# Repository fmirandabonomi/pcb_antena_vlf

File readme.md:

<!-- markdownlint-disable-file MD013 -->
# Antena VLF, Laboratorio de Telecomunicaciones FACET UNT

En este repositorio se encuentran los diseños de los acondicionadores de señales y módulo de adquisición de la antena de VLF desarrollada en el Laboratorio de Telecomunicaciones, FACET UNT en el periodo 2024-2025

La antena de VLF consiste en un par de antenas de lazo dispuestas en cuadratura. Cada antena de lazo es conectada a un acondicionador de señal que cumple las funciones de convertidor corriente/tensión y filtro. La salida de los acondicionadores es adquirida por un módulo de adquisición y transmitida via Ethernet hasta una computadora para su proceso y almacenamiento.

## Contenido

- **/adquisicion** : Directorio conteniendo el proyecto de KiCad del módulo de adquisición.
- **/acondicionador** : Directorio conteniendo el proyecto de KiCad del módulo acondicionador de señal.

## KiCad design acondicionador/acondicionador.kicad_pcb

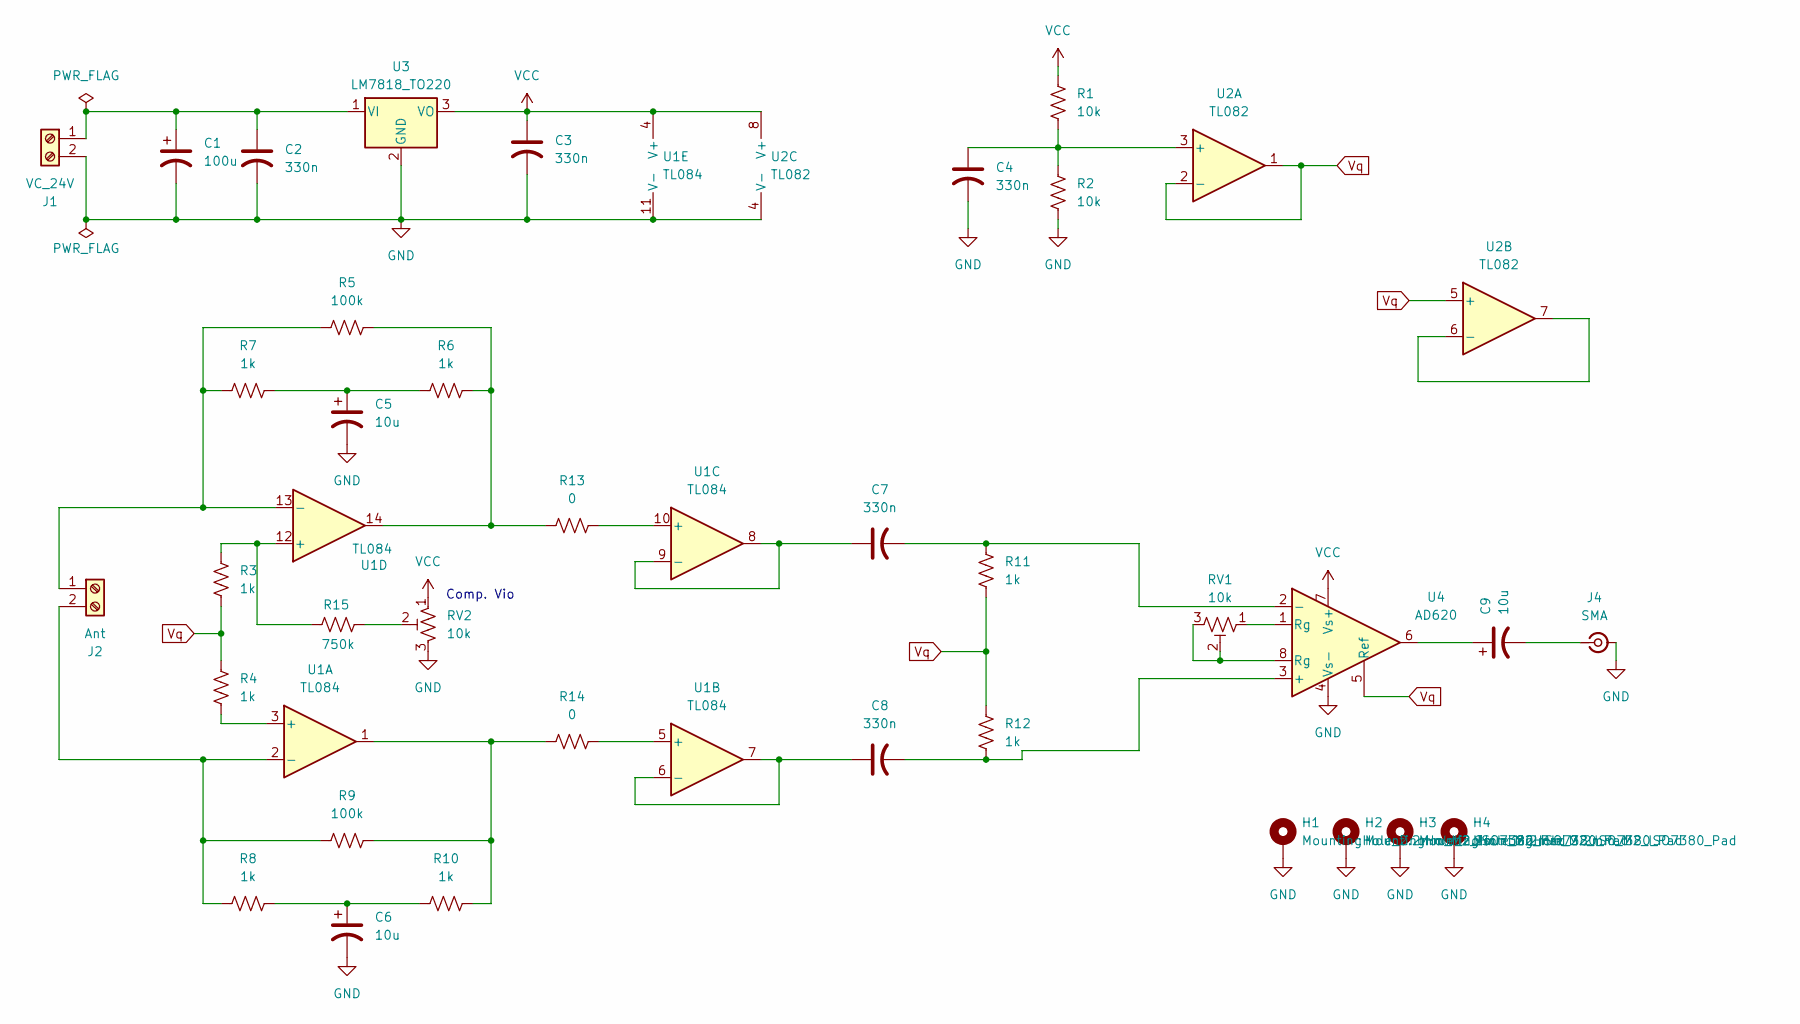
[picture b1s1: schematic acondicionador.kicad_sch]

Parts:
C1: 100u; CP_Radial_D10.0mm_P5.00mm-pad2mm2
C2, C3, C4, C7, C8: 330n; C_Disc_D5.1mm_W3.2mm_P5.00mm-pad2mm
C5, C6, C9: 10u; CP_Radial_D10.0mm_P5.00mm-pad2mm2
H1, H2, H3, H4: MountingHole_2.2mm_M2_ISO7380_Pad
J1: VC_24V; TerminalBlock_MetzConnect_Type011_RT05502HBLC_1x02_P5.00mm_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
J2: Ant; TerminalBlock_MetzConnect_Type011_RT05502HBLC_1x02_P5.00mm_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
J4: SMA; SMA_Samtec_SMA-J-P-H-ST-EM1_EdgeMount
R1, R2: 10k; R_Axial_DIN0207_L6.3mm_D2.5mm_P10.16mm_Horizontal-pad2mm
R3, R4: 1k; R_Axial_DIN0207_L6.3mm_D2.5mm_P15.24mm_Horizontal-pad2mm
R5, R9: 100k; R_Axial_DIN0207_L6.3mm_D2.5mm_P10.16mm_Horizontal-pad2mm
R6, R7, R8, R10, R11, R12: 1k; R_Axial_DIN0207_L6.3mm_D2.5mm_P10.16mm_Horizontal-pad2mm
R13, R14: 0; R_Axial_DIN0207_L6.3mm_D2.5mm_P10.16mm_Horizontal-pad2mm
R15: 750k; R_Axial_DIN0207_L6.3mm_D2.5mm_P10.16mm_Horizontal-pad2mm
RV1, RV2: 10k; Potentiometer_Bourns_3296W_Vertical-pad2mm
U1: TL084; DIP-14_W7.62mm_LongPads-2mm
U2: TL082; DIP-8_W7.62mm_LongPads-pad2mm
U3: LM7818_TO220; TO-220-3_Vertical-pad2mm
U4: AD620; DIP-8_W7.62mm_LongPads-pad2mm

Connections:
GND: C1.2, C2.2, C3.2, C4.2, C5.2, C6.2, H1.1, H2.1, H3.1, H4.1, J1.2, J4.2 (Ext), R2.2, RV2.3, U1.11 (V-), U2.4 (V-), U3.2 (GND), U4.4 (Vs-)
unnamed: C5.1, R6.1, R7.2
unnamed: C6.1, R8.2, R10.1
unnamed: C9.1, U4.6
unnamed: C1.1, C2.1, J1.1, U3.1 (VI)
unnamed: J2.1, R5.1, R7.1, U1.13 (-)
unnamed: J2.2, R8.1, R9.1, U1.2 (-)
unnamed: C9.2, J4.1 (In)
unnamed: R9.2, R10.2, R14.1, U1.1
unnamed: R5.2, R6.2, R13.1, U1.14
unnamed: R15.2, RV2.2
unnamed: RV1.1, U4.1 (Rg)
unnamed: RV1.2, RV1.3, U4.8 (Rg)
unnamed: R4.2, U1.3 (+)
unnamed: R14.2, U1.5 (+)
unnamed: C8.1, U1.6 (-), U1.7
unnamed: R13.2, U1.10 (+)
unnamed: C7.1, U1.8, U1.9 (-)
unnamed: R3.1, R15.1, U1.12 (+)
unnamed: C4.1, R1.2, R2.1, U2.3 (+)
unnamed: U2.6 (-), U2.7
unnamed: C8.2, R12.2, U4.3 (+)
unnamed: C7.2, R11.1, U4.2 (-)
VCC: C3.1, R1.1, RV2.1, U1.4 (V+), U2.8 (V+), U3.3 (VO), U4.7 (Vs+)
Vq: R3.2, R4.1, R11.2, R12.1, U2.1, U2.2 (-), U2.5 (+), U4.5 (Ref)

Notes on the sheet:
Comp. Vio

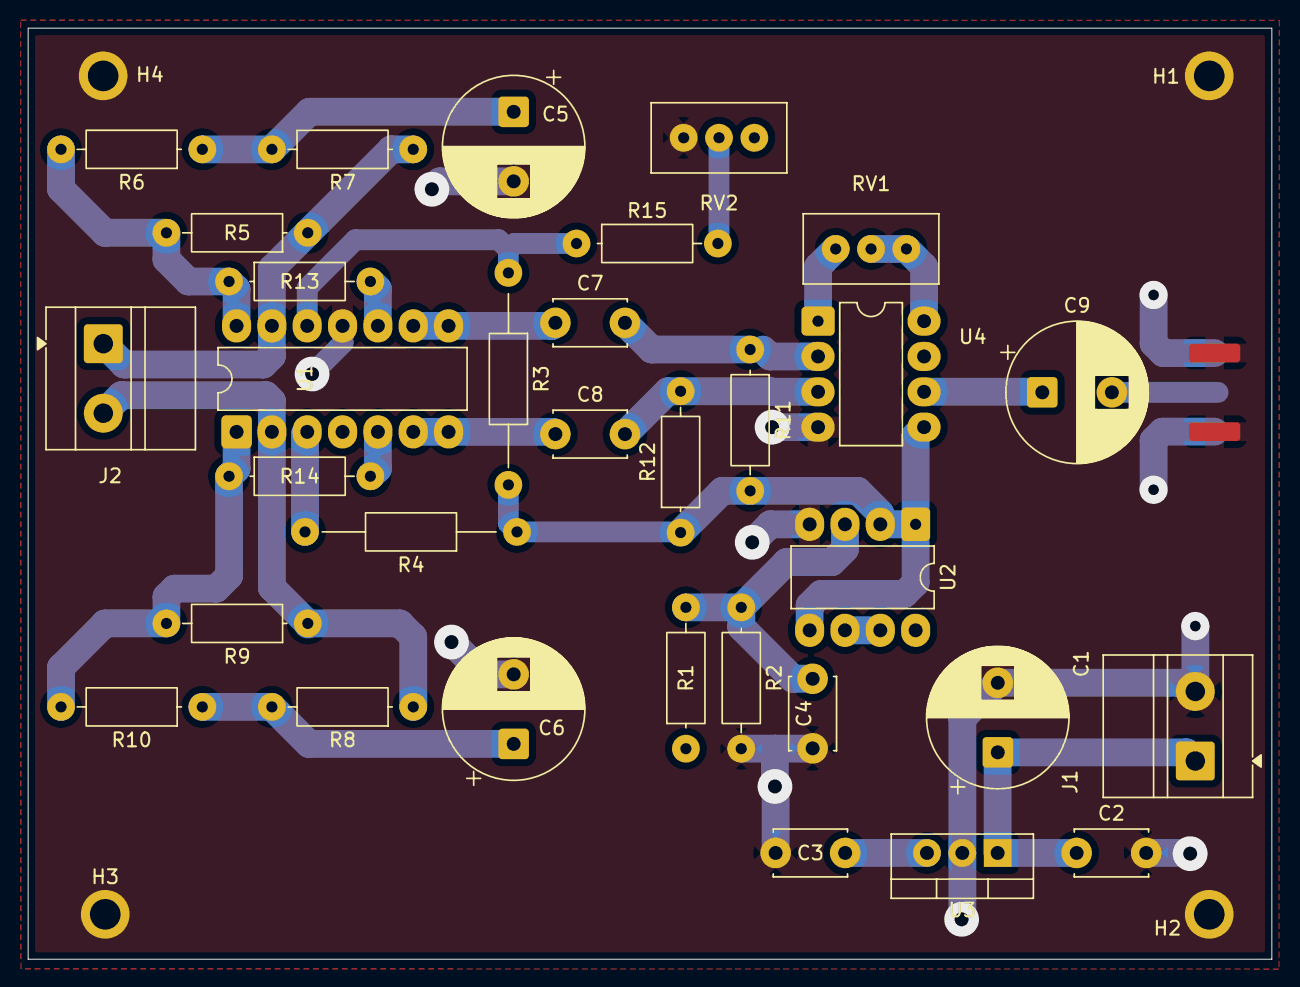
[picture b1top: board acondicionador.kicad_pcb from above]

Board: 2 copper layers, 89.4 x 66.9 mm, 37 parts (1 on the bottom side), 25 nets.

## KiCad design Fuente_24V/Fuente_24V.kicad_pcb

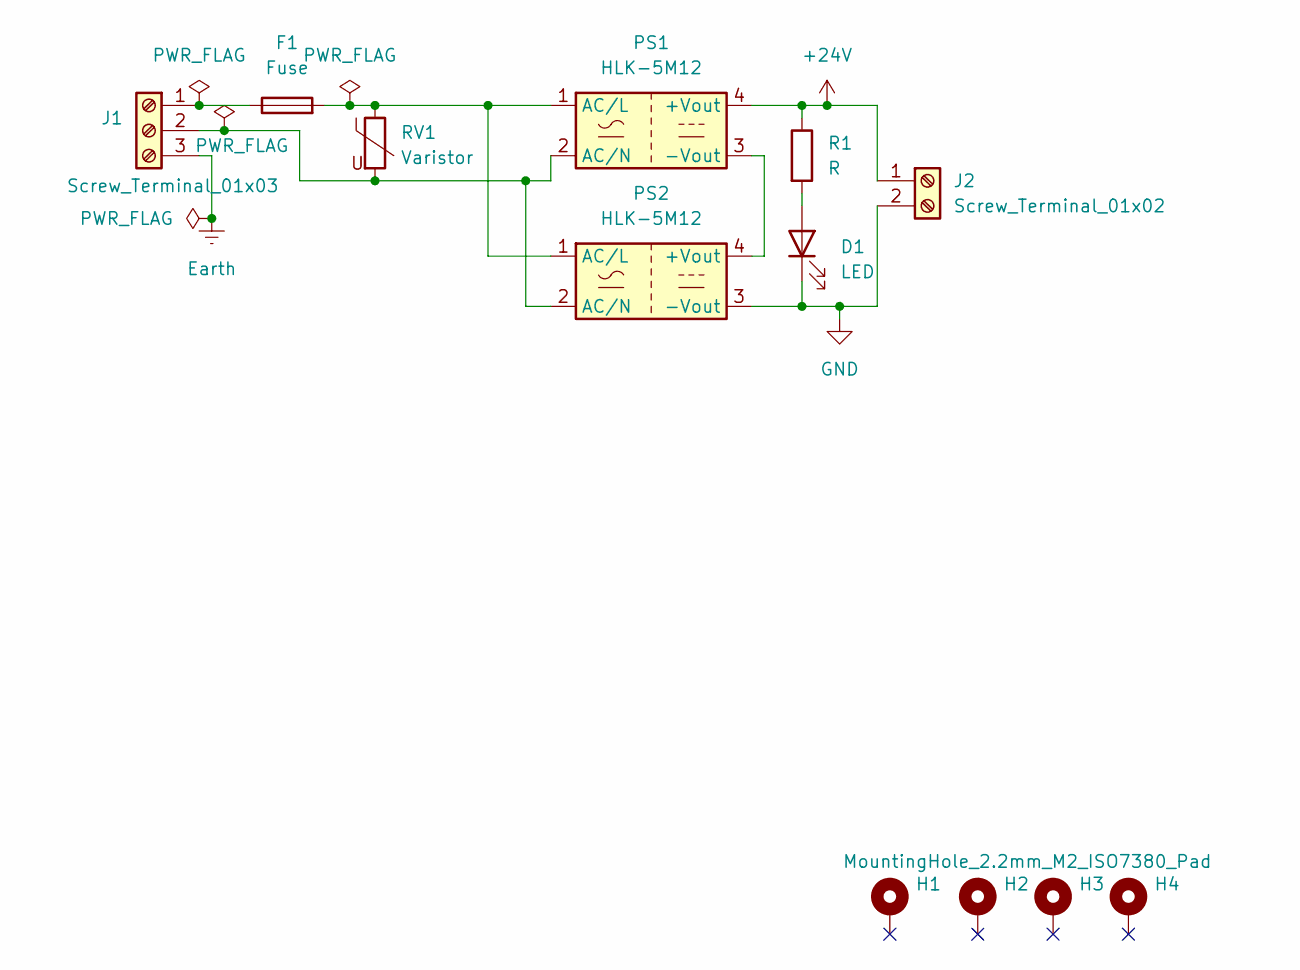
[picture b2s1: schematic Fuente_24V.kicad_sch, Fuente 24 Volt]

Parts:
D1: LED; LED_D3.0mm
F1: Fuse; Fuseholder_Cylinder-5x20mm_Schurter_0031_8201_Horizontal_Op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
H1, H2, H3, H4: MountingHole_2.2mm_M2_ISO7380_Pad
J1: Screw_Terminal_01x03; TerminalBlock_MaiXu_MX126-5.0-03P_1x03_P5.00mm
J2: Screw_Terminal_01x02; TerminalBlock_MaiXu_MX126-5.0-02P_1x02_P5.00mm
PS1, PS2: HLK-5M12; Converter_ACDC_Hi-Link_HLK-5Mxx
R1: R; R_Axial_DIN0207_L6.3mm_D2.5mm_P10.16mm_Horizontal
RV1: Varistor; RV_Disc_D12mm_W4mm_P7.5mm

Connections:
+24V: J2.1, PS1.4 (+Vout), R1.1
Earth: J1.3
GND: D1.1 (K), J2.2, PS2.3 (-Vout)
unnamed: D1.2 (A), R1.2
unnamed: F1.1, J1.1
unnamed: J1.2, PS1.2 (AC/N), PS2.2 (AC/N), RV1.2
unnamed: PS1.3 (-Vout), PS2.4 (+Vout)
unnamed: F1.2, PS1.1 (AC/L), PS2.1 (AC/L), RV1.1

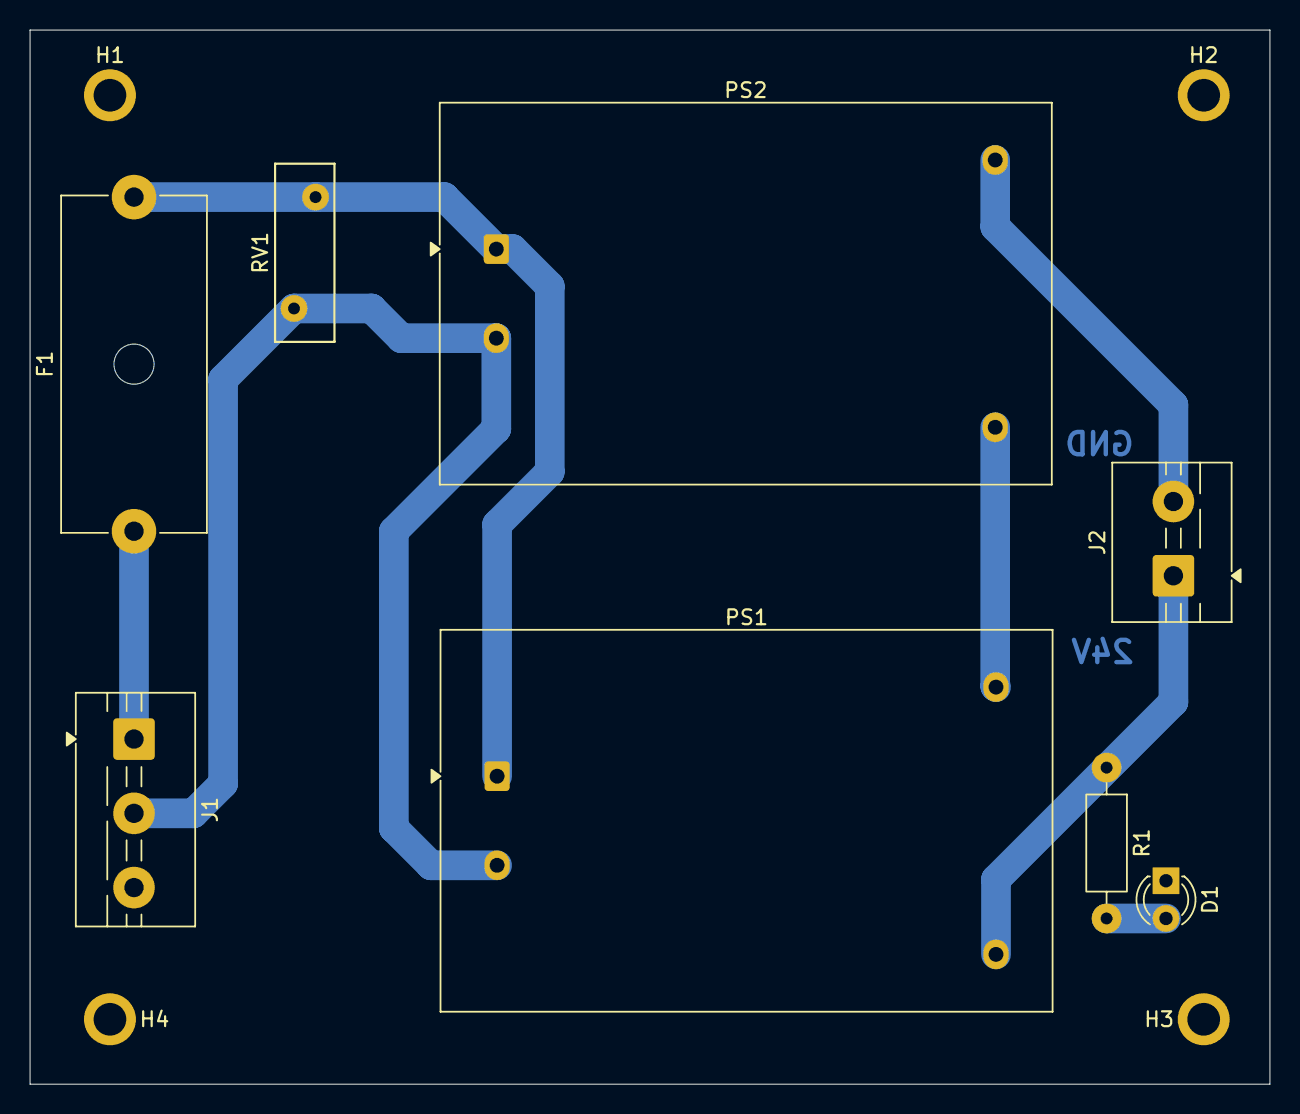
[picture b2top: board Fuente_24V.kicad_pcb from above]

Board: 2 copper layers, 83.5 x 71.0 mm, 12 parts (0 on the bottom side), 7 nets.

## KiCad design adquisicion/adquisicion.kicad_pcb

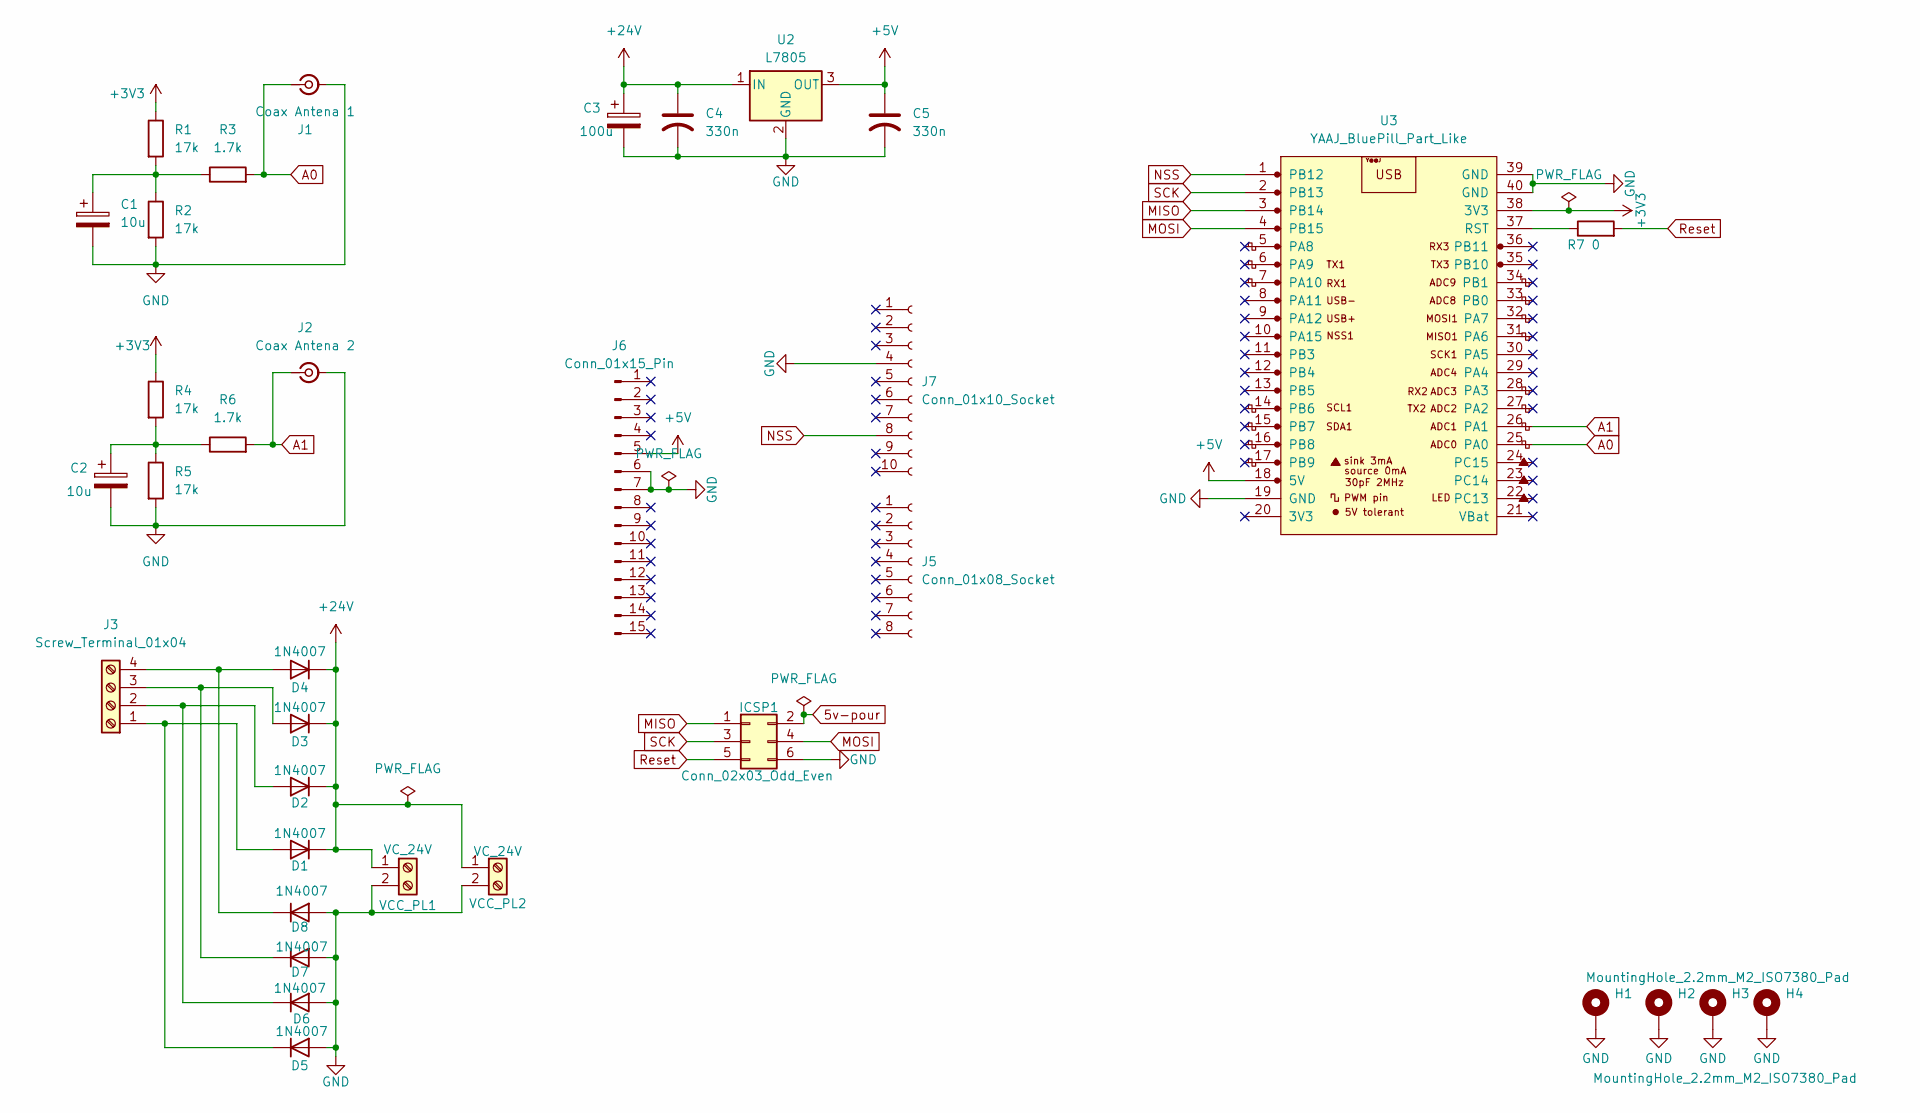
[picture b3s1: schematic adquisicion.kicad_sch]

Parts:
C1, C2: 10u; CP_Radial_D10.0mm_P5.00mm
C3: 100u; CP_Radial_D10.0mm_P5.00mm
C4, C5: 330n; C_Disc_D5.1mm_W3.2mm_P5.00mm-pad2mm
D1, D2, D3, D4, D5, D6, D7, D8: 1N4007; D_DO-41_SOD81_P10.16mm_Horizontal
H1, H2, H3, H4: MountingHole_2.2mm_M2_ISO7380_Pad
ICSP1: Conn_02x03_Odd_Even; PinHeader_2x03_P2.54mm_Vertical
J1: Coax Antena 1; SMA_Samtec_SMA-J-P-H-ST-EM1_EdgeMount
J2: Coax Antena 2; SMA_Samtec_SMA-J-P-H-ST-EM1_EdgeMount
J3: Screw_Terminal_01x04; TerminalBlock_MetzConnect_Type011_RT05504HBLC_1x04_P5.00mm_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
J5: Conn_01x08_Socket; PinHeader_1x08_P2.54mm_Vertical
J6: Conn_01x15_Pin; PinHeader_1x15_P2.54mm_Vertical
J7: Conn_01x10_Socket; PinHeader_1x10_P2.54mm_Vertical
R1, R2, R4, R5: 17k; R_Axial_DIN0207_L6.3mm_D2.5mm_P10.16mm_Horizontal-pad2mm
R3, R6: 1.7k; R_Axial_DIN0207_L6.3mm_D2.5mm_P10.16mm_Horizontal-pad2mm
R7: 0; R_Axial_DIN0207_L6.3mm_D2.5mm_P15.24mm_Horizontal-pad2mm
U2: L7805; TO-220-3_Vertical
U3: YAAJ_BluePill_Part_Like; YAAJ_BluePill_2
VCC_PL1, VCC_PL2: VC_24V; TerminalBlock_MetzConnect_Type011_RT05502HBLC_1x02_P5.00mm_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

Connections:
5v-pour: ICSP1.2
+3V3: R1.1, R4.1, U3.38 (3V3)
+5V: C5.1, J6.5, U2.3 (OUT), U3.18 (5V)
+24V: C3.1, C4.1, D1.1 (K), D2.1 (K), D3.1 (K), D4.1 (K), U2.1 (IN), VCC_PL1.1, VCC_PL2.1
A0: J1.1 (In), R3.2, U3.25 (PA0)
A1: J2.1 (In), R6.2, U3.26 (PA1)
GND: C1.2, C2.2, C3.2, C4.2, C5.2, D5.2 (A), D6.2 (A), D7.2 (A), D8.2 (A), H1.1, H2.1, H3.1, H4.1, ICSP1.6, J1.2 (Ext), J2.2 (Ext), J6.6, J6.7, J7.4, R2.2, R5.2, U2.2 (GND), U3.19 (GND), U3.39 (GND), U3.40 (GND), VCC_PL1.2, VCC_PL2.2
MISO: ICSP1.1, U3.3 (PB14)
MOSI: ICSP1.4, U3.4 (PB15)
NSS: J7.8, U3.1 (PB12)
unnamed: C1.1, R1.2, R2.1, R3.1
unnamed: C2.1, R4.2, R5.1, R6.1
unnamed: D1.2 (A), D5.1 (K), J3.1
unnamed: D2.2 (A), D6.1 (K), J3.2
unnamed: D3.2 (A), D7.1 (K), J3.3
unnamed: D4.2 (A), D8.1 (K), J3.4
unnamed: R7.1, U3.37 (RST)
Reset: ICSP1.5, R7.2
SCK: ICSP1.3, U3.2 (PB13)

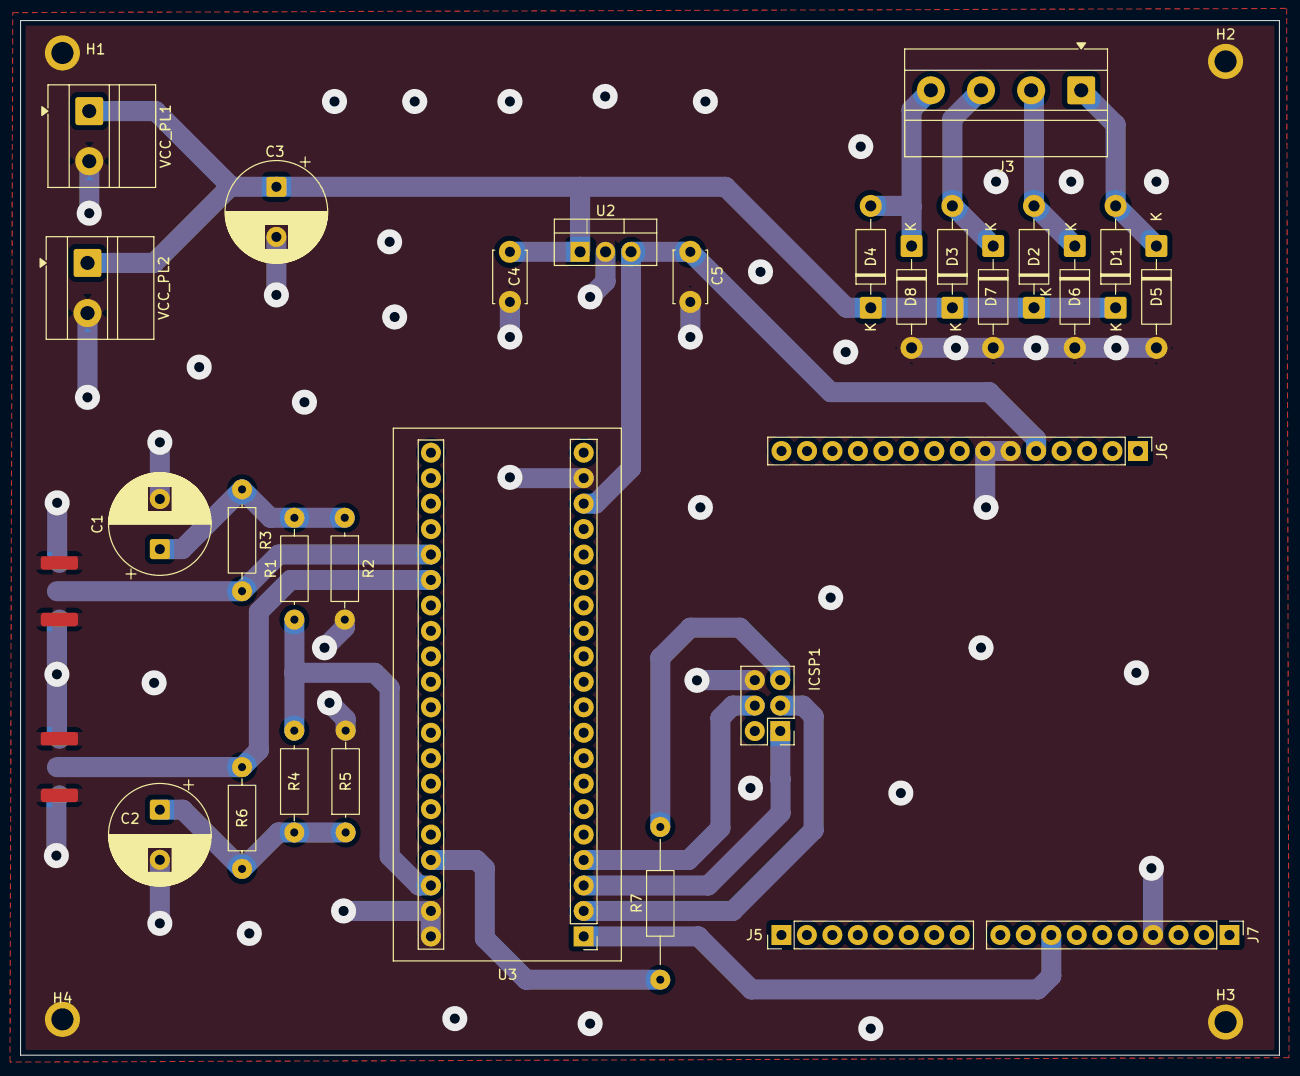
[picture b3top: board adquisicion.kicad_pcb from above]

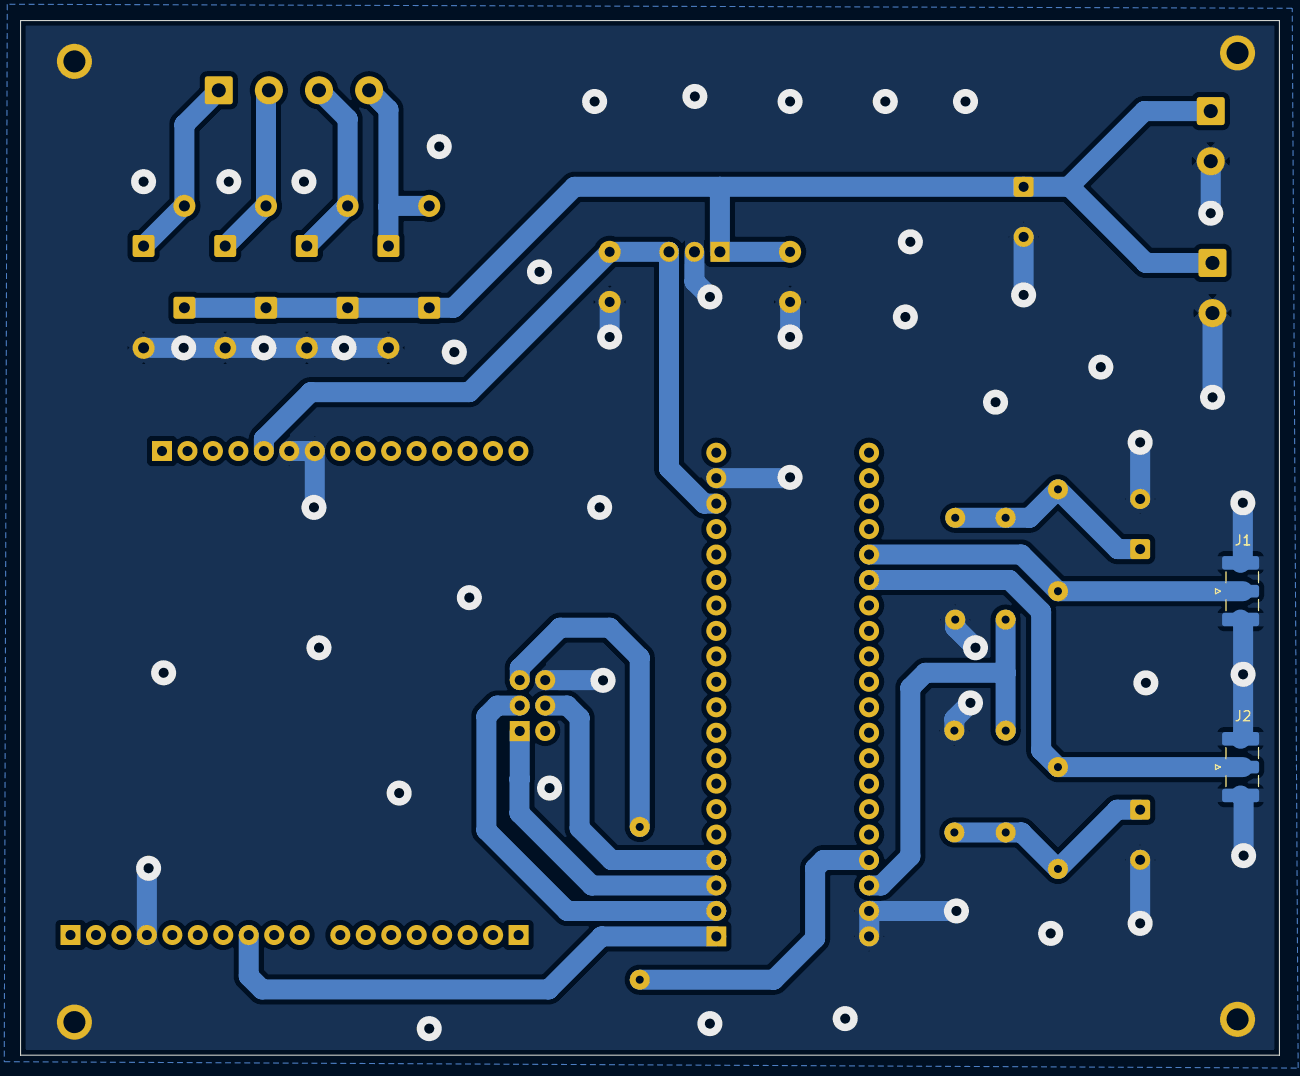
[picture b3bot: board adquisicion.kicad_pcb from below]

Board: 2 copper layers, 125.6 x 103.2 mm, 35 parts (2 on the bottom side), 18 nets.

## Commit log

2025-08-19 Versión inicial
2025-08-20 Pasaje de componentes y netlist a pcb
2025-08-21 Versión lista para imprimir
2025-08-28 Se agrego la otra placa en carpeta una nueva carpeta. Para revisión
2025-08-29 Organización del repositorio
2025-08-29 Cambio de nombres de proyectos kicad
2025-08-29 Mejoras layout, corrección ERC y DRC
2025-09-05 Modificación posición C5 C6 en placa Acondicionador y cambio de huella sma (verificar), cambio de huella sma en placa Adquisición (verificar)
2025-09-10 se modifica la disposición de los elementos
2025-09-16 Se genera un nuevo proyecto para fuente
2025-09-17 Se agrega el gitIgnore para el proyecto
2025-09-17 Se agrega el esquemático y pcb de Fuente
2025-09-19 Se modifica el gitignore para ignorar una carpeta
2025-09-19 se agrega led indicador de fuente al esquema
2025-12-02 Compensación Voi acondicionador
